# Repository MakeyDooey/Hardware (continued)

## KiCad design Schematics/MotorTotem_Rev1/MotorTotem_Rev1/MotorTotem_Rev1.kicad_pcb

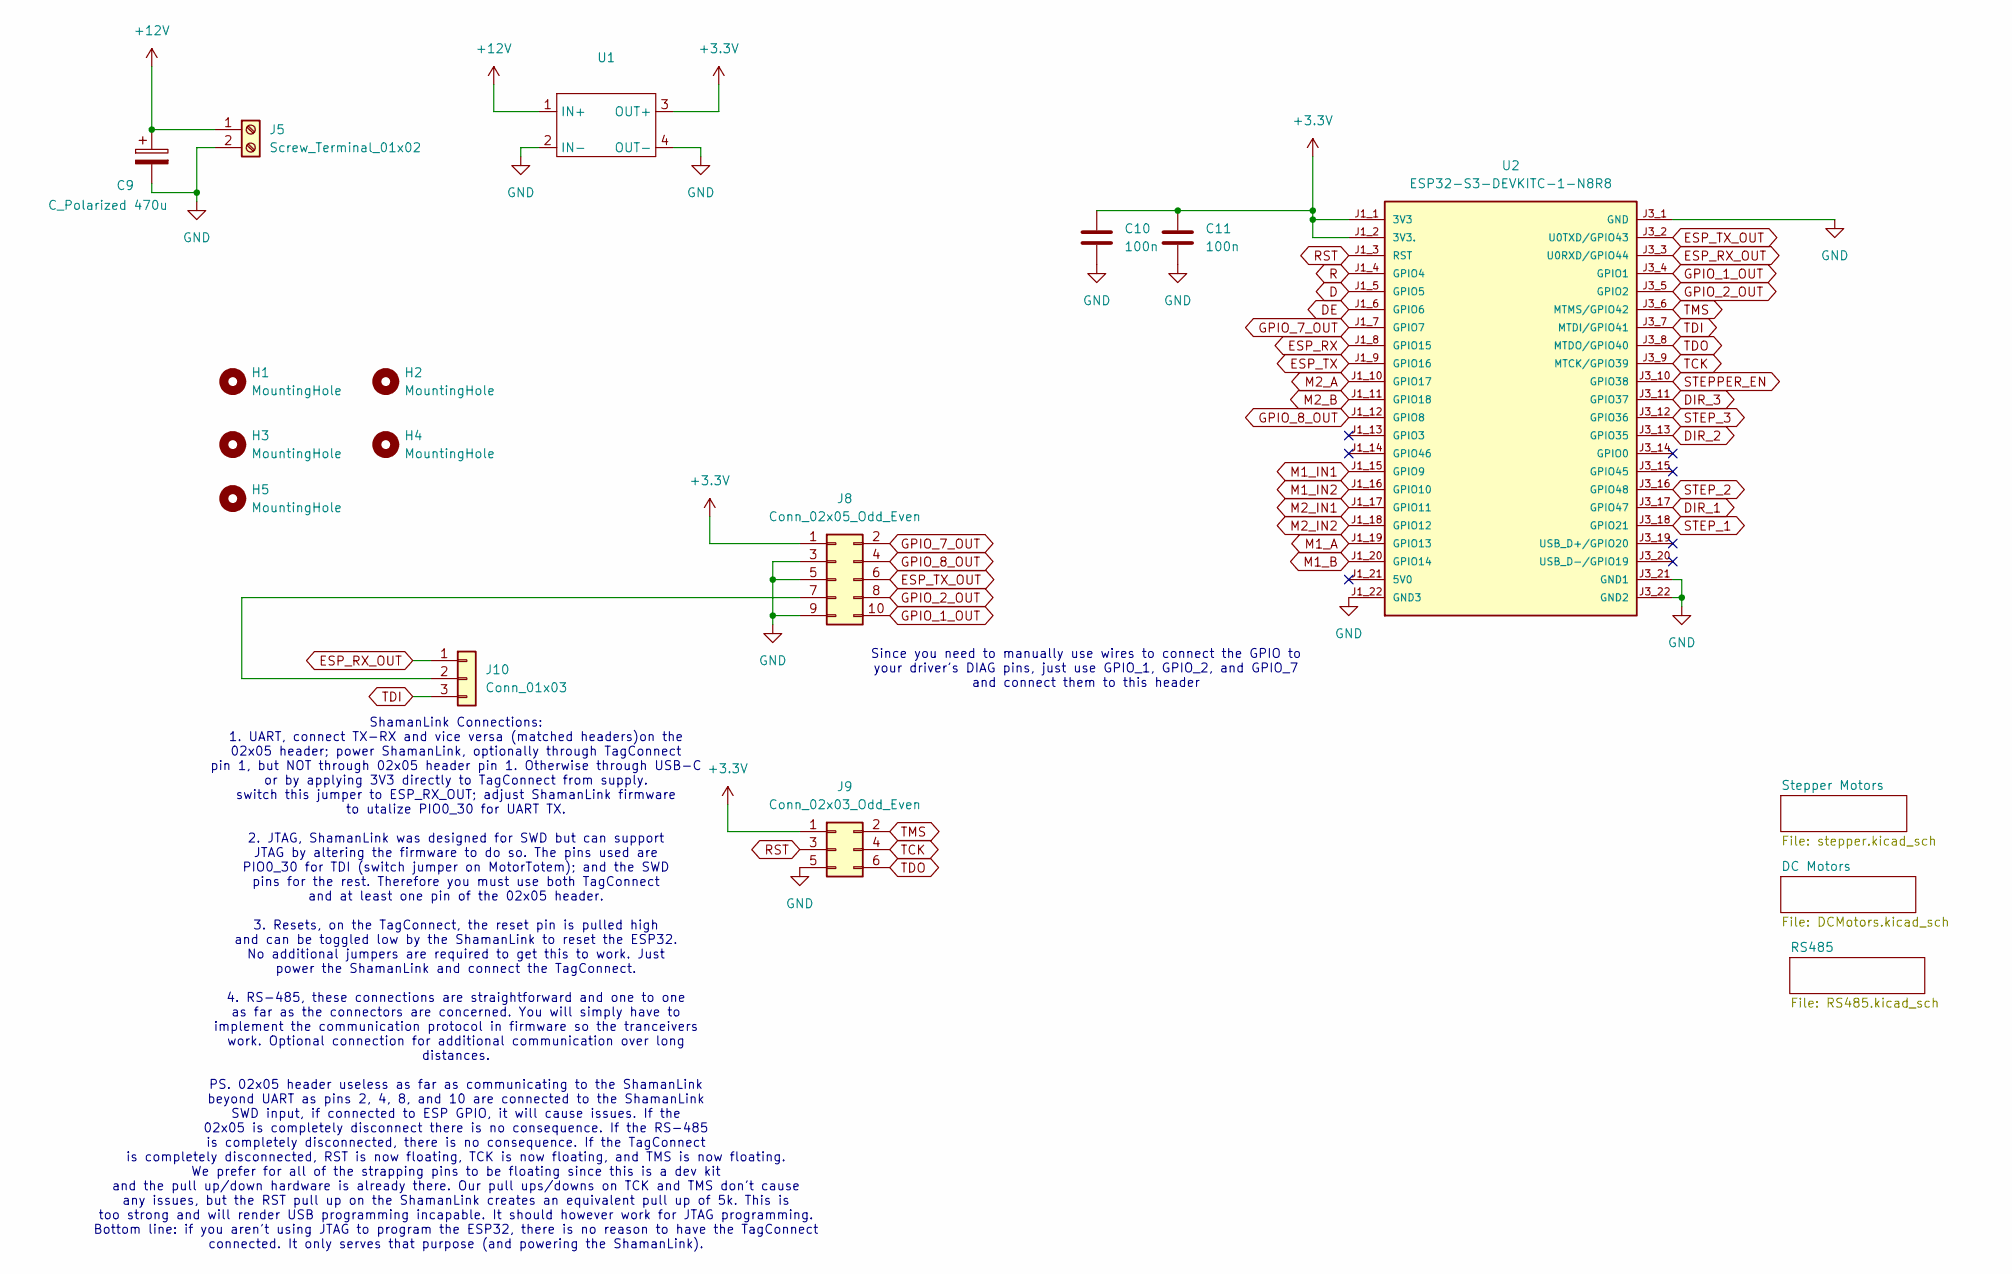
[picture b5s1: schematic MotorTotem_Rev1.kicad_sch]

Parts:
C9: C_Polarized 470u; CP_Radial_D6.3mm_P2.50mm
C10, C11: 100n; C_0805_2012Metric_Pad1.18x1.45mm_HandSolder
H1, H2, H3, H4, H5: MountingHole; MountingHole_2.5mm_Pad_TopOnly
J5: Screw_Terminal_01x02; TerminalBlock_Phoenix_MKDS-1,5-2-5.08_1x02_P5.08mm_Horizont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
J8: Conn_02x05_Odd_Even; PinHeader_2x05_P2.54mm_Vertical
J9: Conn_02x03_Odd_Even; PinHeader_2x03_P2.54mm_Vertical
J10: Conn_01x03; PinHeader_1x03_P2.54mm_Vertical
U1: LM2596BuckBoost
U2: ESP32-S3-DEVKITC-1-N8R8

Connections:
+3.3V: C10.1, C11.1, J8.1, J9.1, U1.3 (OUT+), U2.J1_1 (3V3), U2.J1_2 (3V3.); also elsewhere on the board
+12V: C9.1, J5.1, U1.1 (IN+); also elsewhere on the board
D: U2.J1_5 (GPIO5); also elsewhere on the board
DE: U2.J1_6 (GPIO6); also elsewhere on the board
DIR_1: U2.J3_17 (GPIO47); also elsewhere on the board
DIR_2: U2.J3_13 (GPIO35); also elsewhere on the board
DIR_3: U2.J3_11 (GPIO37); also elsewhere on the board
ESP_RX: U2.J1_8 (GPIO15); also elsewhere on the board
ESP_RX_OUT: J10.1, U2.J3_3 (U0RXD/GPIO44)
ESP_TX: U2.J1_9 (GPIO16); also elsewhere on the board
ESP_TX_OUT: J8.6, U2.J3_2 (U0TXD/GPIO43)
GND: C9.2, C10.2, C11.2, J5.2, J8.3, J8.5, J8.9, J9.5, U1.2 (IN-), U1.4 (OUT-), U2.J1_22 (GND3), U2.J3_1 (GND), U2.J3_21 (GND1), U2.J3_22 (GND2); also elsewhere on the board
GPIO_1_OUT: J8.10, U2.J3_4 (GPIO1)
GPIO_2_OUT: J8.8, U2.J3_5 (GPIO2)
GPIO_7_OUT: J8.2, U2.J1_7 (GPIO7)
GPIO_8_OUT: J8.4, U2.J1_12 (GPIO8)
M1_A: U2.J1_19 (GPIO13); also elsewhere on the board
M1_B: U2.J1_20 (GPIO14); also elsewhere on the board
M1_IN1: U2.J1_15 (GPIO9); also elsewhere on the board
M1_IN2: U2.J1_16 (GPIO10); also elsewhere on the board
M2_A: U2.J1_10 (GPIO17); also elsewhere on the board
M2_B: U2.J1_11 (GPIO18); also elsewhere on the board
M2_IN1: U2.J1_17 (GPIO11); also elsewhere on the board
M2_IN2: U2.J1_18 (GPIO12); also elsewhere on the board
unnamed: J8.7, J10.2
R: U2.J1_4 (GPIO4); also elsewhere on the board
RST: J9.3, U2.J1_3 (RST)
STEPPER_EN: U2.J3_10 (GPIO38); also elsewhere on the board
STEP_1: U2.J3_18 (GPIO21); also elsewhere on the board
STEP_2: U2.J3_16 (GPIO48); also elsewhere on the board
STEP_3: U2.J3_12 (GPIO36); also elsewhere on the board
TCK: J9.4, U2.J3_9 (MTCK/GPIO39)
TDI: J10.3, U2.J3_7 (MTDI/GPIO41)
TDO: J9.6, U2.J3_8 (MTDO/GPIO40)
TMS: J9.2, U2.J3_6 (MTMS/GPIO42)

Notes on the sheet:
Since you need to manually use wires to connect the GPIO to your driver's DIAG pins, just use GPIO_1, GPIO_2, and GPIO_7 and connect them to this header
ShamanLink Connections: 1. UART, connect TX-RX and vice versa (matched headers)on the 02x05 header; power ShamanLink, optionally through TagConnect pin 1, but NOT through 02x05 header pin 1. Otherwise through USB-C or by applying 3V3 directly to TagConnect from supply. switch this jumper to ESP_RX_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

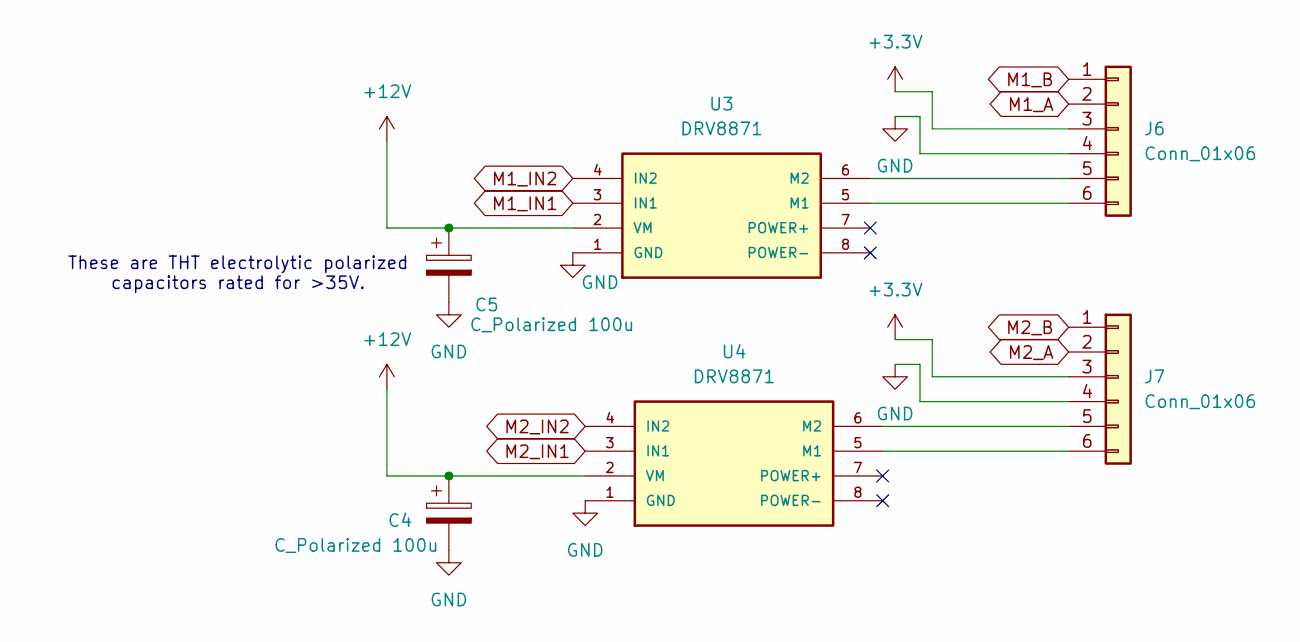
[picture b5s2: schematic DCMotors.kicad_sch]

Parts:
C4, C5: C_Polarized 100u; CP_Radial_D6.3mm_P2.50mm
J6, J7: Conn_01x06; PinHeader_1x06_P2.54mm_Vertical
U3, U4: DRV8871

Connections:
+3.3V: J6.3, J7.3; also elsewhere on the board
+12V: C4.1, C5.1, U3.2 (VM), U4.2 (VM); also elsewhere on the board
GND: C4.2, C5.2, J6.4, J7.4, U3.1 (GND), U4.1 (GND); also elsewhere on the board
M1_A: J6.2; also elsewhere on the board
M1_B: J6.1; also elsewhere on the board
M1_IN1: U3.3 (IN1); also elsewhere on the board
M1_IN2: U3.4 (IN2); also elsewhere on the board
M2_A: J7.2; also elsewhere on the board
M2_B: J7.1; also elsewhere on the board
M2_IN1: U4.3 (IN1); also elsewhere on the board
M2_IN2: U4.4 (IN2); also elsewhere on the board
unnamed: J6.5, U3.6 (M2)
unnamed: J6.6, U3.5 (M1)
unnamed: J7.5, U4.6 (M2)
unnamed: J7.6, U4.5 (M1)

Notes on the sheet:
These are THT electrolytic polarized capacitors rated for >35V.

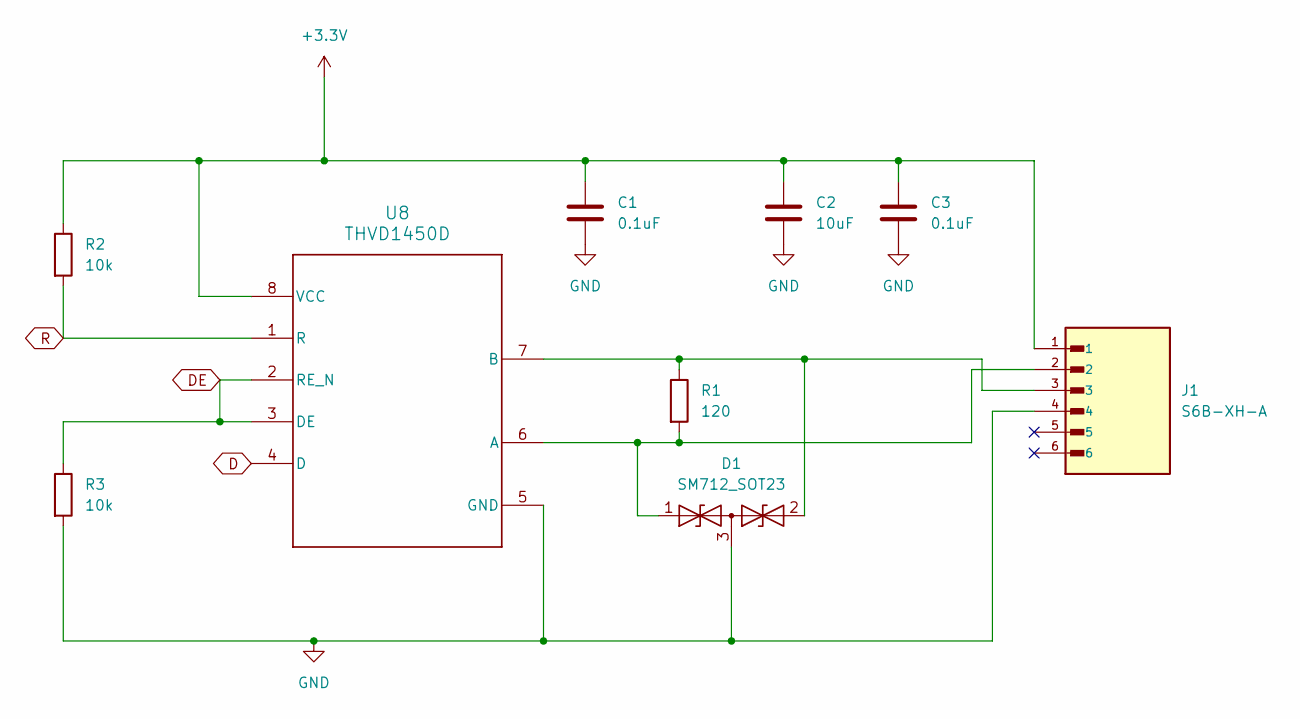
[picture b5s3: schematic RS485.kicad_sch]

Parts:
C1, C3: 0.1uF; C_0805_2012Metric_Pad1.18x1.45mm_HandSolder
C2: 10uF; C_0805_2012Metric_Pad1.18x1.45mm_HandSolder
D1: SM712_SOT23; SOT-23
J1: S6B-XH-A; JST_S6B-XH-A
R1: 120; R_1206_3216Metric_Pad1.30x1.75mm_HandSolder
R2, R3: 10k; R_0805_2012Metric_Pad1.20x1.40mm_HandSolder
U8: THVD1450D; D0008A_M

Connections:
+3.3V: C1.1, C2.1, C3.1, J1.1, R2.1, U8.8 (VCC); also elsewhere on the board
D: U8.4 (D); also elsewhere on the board
DE: R3.1, U8.2 (RE_N), U8.3 (DE); also elsewhere on the board
GND: C1.2, C2.2, C3.2, D1.3 (common), J1.4, R3.2, U8.5 (GND); also elsewhere on the board
unnamed: D1.1 (A1), J1.2, R1.2, U8.6 (A)
unnamed: D1.2 (A2), J1.3, R1.1, U8.7 (B)
R: R2.2, U8.1 (R); also elsewhere on the board

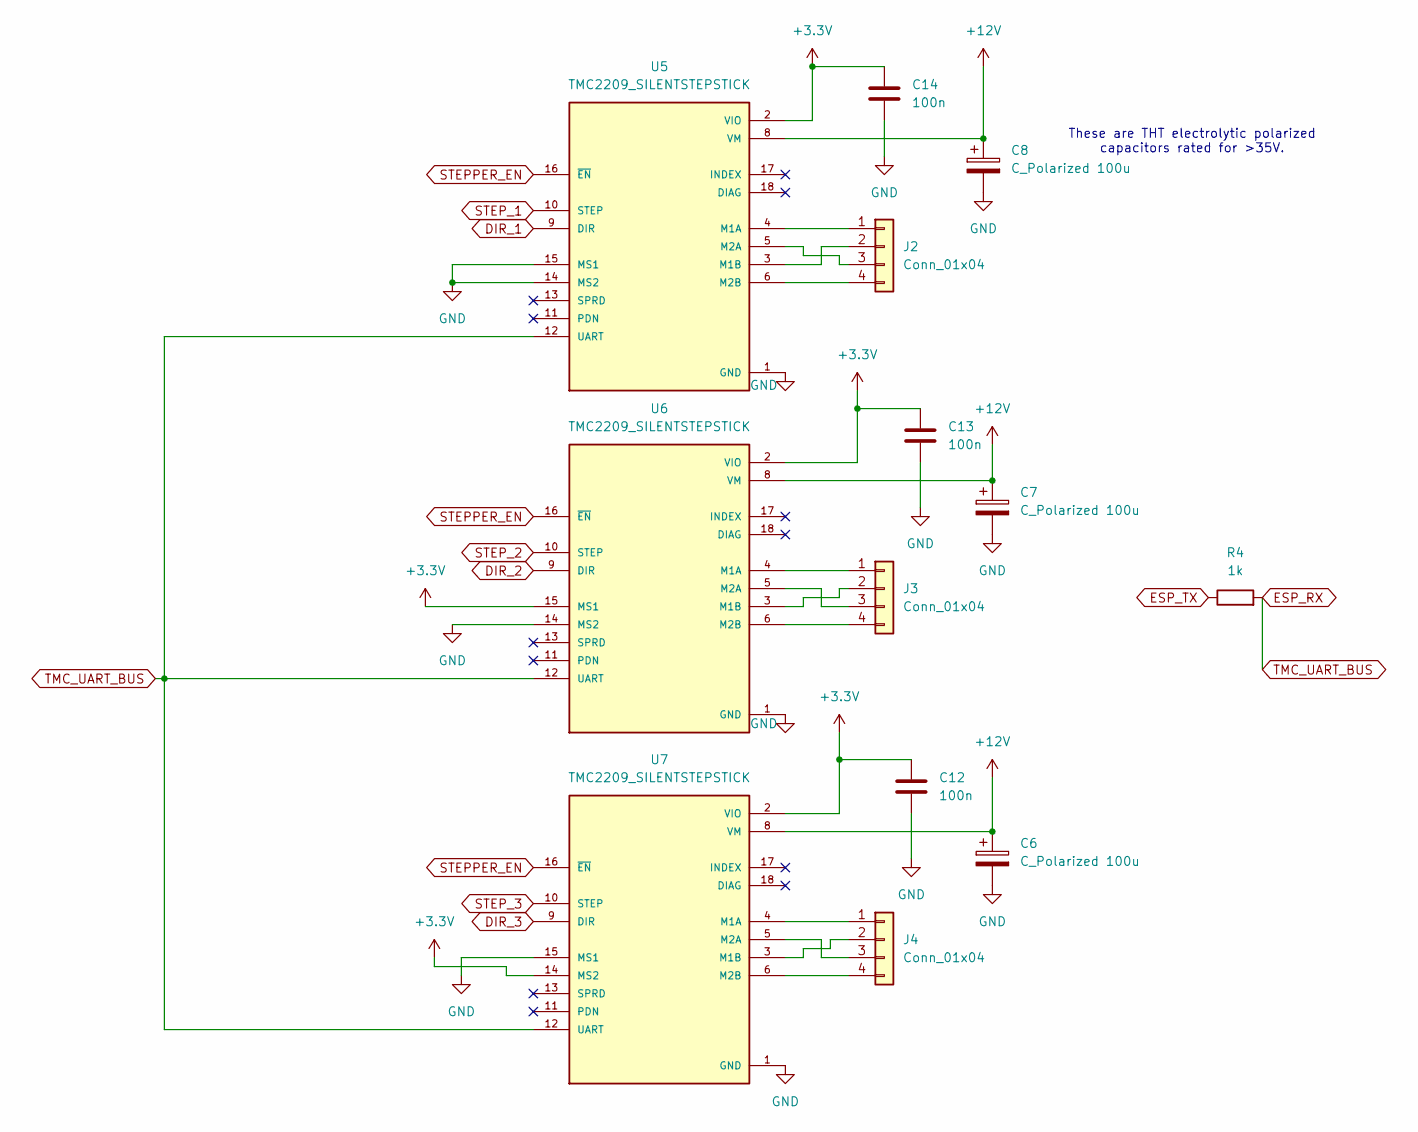
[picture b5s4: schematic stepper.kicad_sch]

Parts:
C6, C7, C8: C_Polarized 100u; CP_Radial_D6.3mm_P2.50mm
C12, C13, C14: 100n; C_0805_2012Metric_Pad1.18x1.45mm_HandSolder
J2, J3, J4: Conn_01x04; PinHeader_1x04_P2.54mm_Vertical
R4: 1k; R_0805_2012Metric_Pad1.20x1.40mm_HandSolder
U5, U6, U7: TMC2209_SILENTSTEPSTICK; MODULE_TMC2209_SILENTSTEPSTICK; PARTREV 1.20

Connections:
+3.3V: C12.1, C13.1, C14.1, U5.2 (VIO), U6.2 (VIO), U6.15 (MS1), U7.2 (VIO), U7.14 (MS2); also elsewhere on the board
+12V: C6.1, C7.1, C8.1, U5.8 (VM), U6.8 (VM), U7.8 (VM); also elsewhere on the board
DIR_1: U5.9 (DIR); also elsewhere on the board
DIR_2: U6.9 (DIR); also elsewhere on the board
DIR_3: U7.9 (DIR); also elsewhere on the board
ESP_RX: R4.2, U5.12 (UART), U6.12 (UART), U7.12 (UART); also elsewhere on the board
ESP_TX: R4.1; also elsewhere on the board
GND: C6.2, C7.2, C8.2, C12.2, C13.2, C14.2, U5.1 (GND), U5.7 (GND), U5.14 (MS2), U5.15 (MS1), U6.1 (GND), U6.7 (GND), U6.14 (MS2), U7.1 (GND), U7.7 (GND), U7.15 (MS1); also elsewhere on the board
unnamed: J2.1, U5.4 (M1A)
unnamed: J2.2, U5.3 (M1B)
unnamed: J2.3, U5.5 (M2A)
unnamed: J2.4, U5.6 (M2B)
unnamed: J3.1, U6.4 (M1A)
unnamed: J3.2, U6.3 (M1B)
unnamed: J3.3, U6.5 (M2A)
unnamed: J3.4, U6.6 (M2B)
unnamed: J4.1, U7.4 (M1A)
unnamed: J4.2, U7.3 (M1B)
unnamed: J4.3, U7.5 (M2A)
unnamed: J4.4, U7.6 (M2B)
STEPPER_EN: U5.16 (~EN), U6.16 (~EN), U7.16 (~EN); also elsewhere on the board
STEP_1: U5.10 (STEP); also elsewhere on the board
STEP_2: U6.10 (STEP); also elsewhere on the board
STEP_3: U7.10 (STEP); also elsewhere on the board

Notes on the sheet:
These are THT electrolytic polarized capacitors rated for >35V.

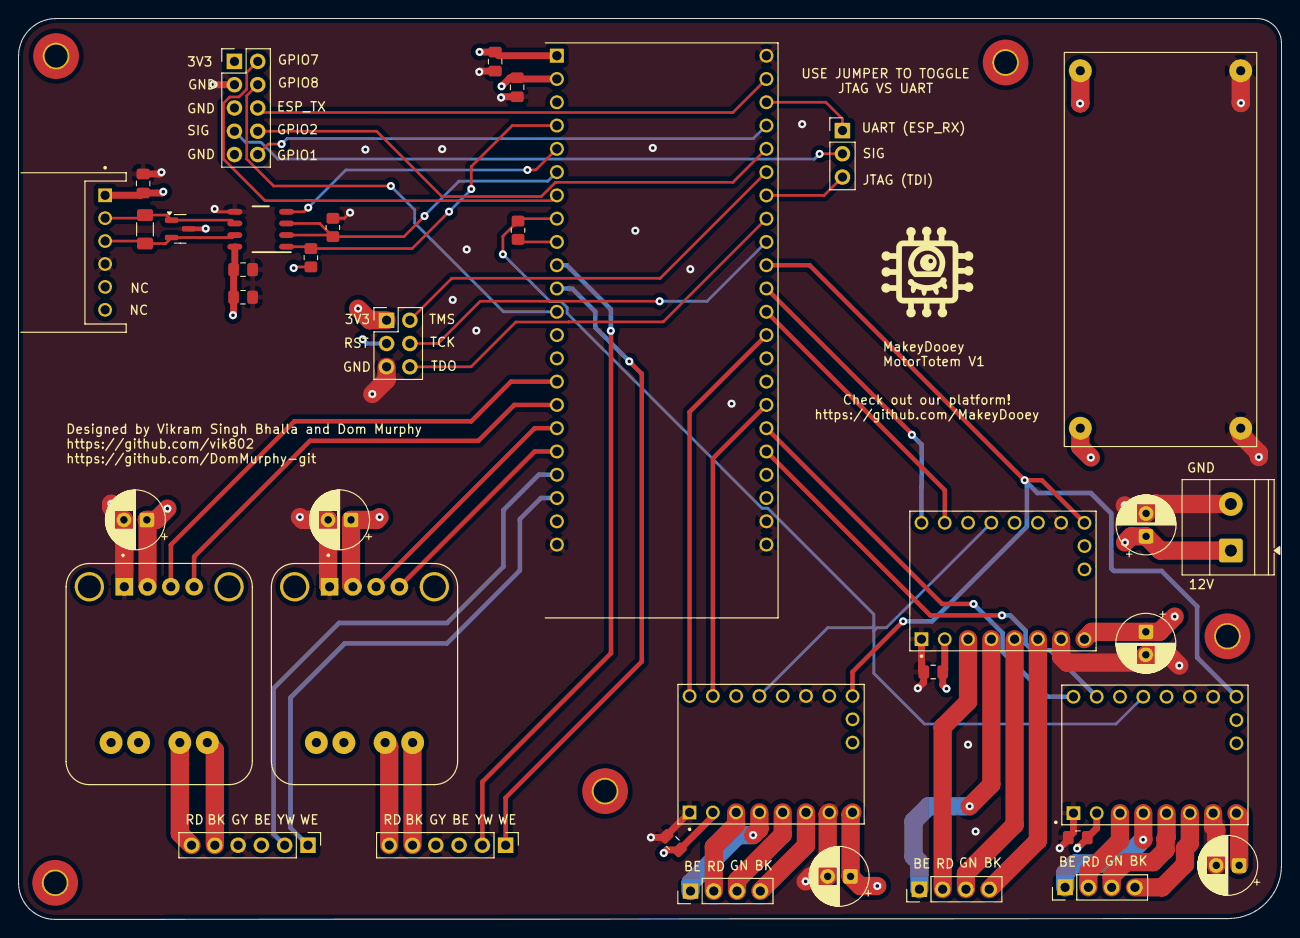
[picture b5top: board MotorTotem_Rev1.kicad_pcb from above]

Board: 4 copper layers, 137.8 x 98.3 mm, 42 parts (0 on the bottom side), 53 nets.

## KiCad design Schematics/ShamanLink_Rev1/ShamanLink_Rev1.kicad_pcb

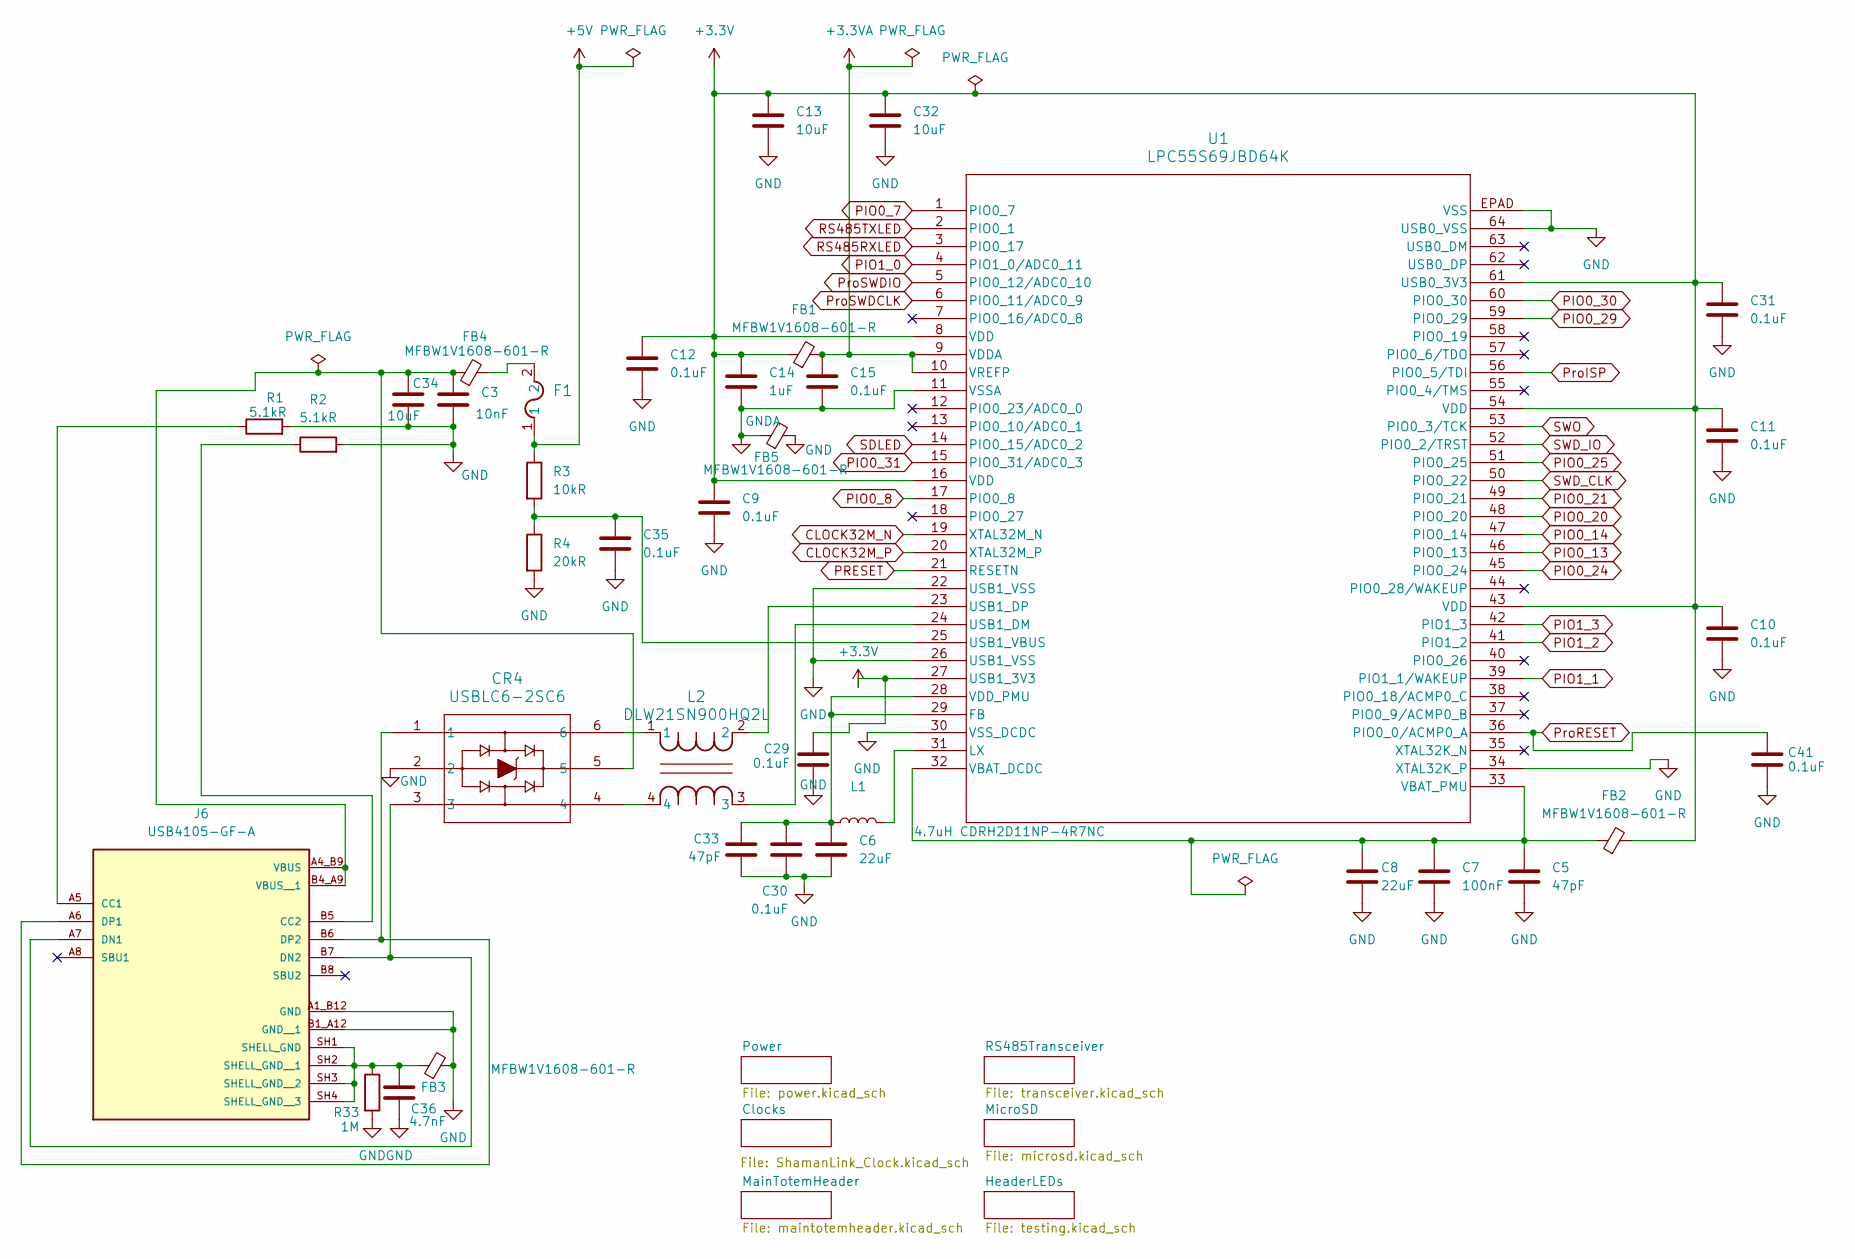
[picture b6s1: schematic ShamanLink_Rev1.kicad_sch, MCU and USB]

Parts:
C3: 10nF; C_0805_2012Metric_Pad1.18x1.45mm_HandSolder
C5, C33: 47pF; C_0805_2012Metric_Pad1.18x1.45mm_HandSolder
C6, C8: 22uF; C_1206_3216Metric_Pad1.33x1.80mm_HandSolder
C7: 100nF; C_0805_2012Metric_Pad1.18x1.45mm_HandSolder
C9, C10, C11, C12, C15, C29, C30, C31, C35, C41: 0.1uF; C_0805_2012Metric_Pad1.18x1.45mm_HandSolder
C13, C32, C34: 10uF; C_0805_2012Metric_Pad1.18x1.45mm_HandSolder
C14: 1uF; C_0805_2012Metric_Pad1.18x1.45mm_HandSolder
C36: 4.7nF; C_0805_2012Metric_Pad1.18x1.45mm_HandSolder
CR4: USBLC6-2SC6; SOT23-6L_STM-M
F1: 1206L075/13.2WR; 1206LSeries_LTF-M
FB1, FB2, FB3, FB4, FB5: MFBW1V1608-601-R; R_0603_1608Metric_Pad0.98x0.95mm_HandSolder
J6: USB4105-GF-A; GCT_USB4105-GF-A; PARTREV B4
L1: 4.7uH CDRH2D11NP-4R7NC; Inductor_Sumida_CDRH2D11
L2: DLW21SN900HQ2L; IND_DLW21S_0805_MUR-M
R1, R2: 5.1kR; R_0805_2012Metric_Pad1.20x1.40mm_HandSolder
R3: 10kR; R_0805_2012Metric_Pad1.20x1.40mm_HandSolder
R4: 20kR; R_0805_2012Metric_Pad1.20x1.40mm_HandSolder
R33: 1M; R_0805_2012Metric_Pad1.20x1.40mm_HandSolder
U1: LPC55S69JBD64K; HTQFP64_SOT855-5_NXP-M

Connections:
+3.3V: C9.1, C10.1, C11.1, C12.1, C13.1, C14.1, C29.1, C31.1, C32.1, FB1.1, FB2.2, U1.8 (VDD), U1.16 (VDD), U1.27 (USB1_3V3), U1.43 (VDD), U1.54 (VDD), U1.61 (USB0_3V3); also elsewhere on the board
+3.3VA: C15.1, FB1.2, U1.9 (VDDA), U1.10 (VREFP)
+5V: F1.1, R3.1; also elsewhere on the board
CLOCK32M_N: U1.19 (XTAL32M_N); also elsewhere on the board
CLOCK32M_P: U1.20 (XTAL32M_P); also elsewhere on the board
GND: C3.2, C5.2, C6.2, C7.2, C8.2, C9.2, C10.2, C11.2, C12.2, C13.2, C29.2, C30.2, C31.2, C32.2, C33.2, C34.2, C35.2, C36.2, C41.2, CR4.2, FB3.2, FB5.2, J6.A1_B12 (GND), J6.B1_A12 (GND__1), R1.2, R2.2, R4.2, R33.2, U1.22 (USB1_VSS), U1.26 (USB1_VSS), U1.30 (VSS_DCDC), U1.34 (XTAL32K_P), U1.64 (USB0_VSS), U1.EPAD (VSS); also elsewhere on the board
GNDA: C14.2, C15.2, FB5.1, U1.11 (VSSA)
unnamed: CR4.4, L2.4
unnamed: CR4.6, L2.1
unnamed: F1.2, FB4.2
unnamed: J6.A5 (CC1), R1.1
unnamed: J6.B5 (CC2), R2.1
unnamed: CR4.3, J6.A7 (DN1), J6.B7 (DN2)
unnamed: CR4.1, J6.A6 (DP1), J6.B6 (DP2)
unnamed: C36.1, FB3.1, J6.SH1 (SHELL_GND), J6.SH2 (SHELL_GND__1), J6.SH3 (SHELL_GND__2), J6.SH4 (SHELL_GND__3), R33.1
unnamed: C3.1, C34.1, CR4.5, FB4.1, J6.A4_B9 (VBUS), J6.B4_A9 (VBUS__1)
unnamed: C6.1, C30.1, C33.1, L1.1, U1.28 (VDD_PMU), U1.29 (FB)
unnamed: L1.2, U1.31 (LX)
unnamed: L2.3, U1.24 (USB1_DM)
unnamed: L2.2, U1.23 (USB1_DP)
unnamed: C35.1, R3.2, R4.1, U1.25 (USB1_VBUS)
unnamed: C5.1, C7.1, C8.1, FB2.1, U1.32 (VBAT_DCDC), U1.33 (VBAT_PMU)
PIO0_7: U1.1 (PIO0_7); also elsewhere on the board
PIO0_8: U1.17 (PIO0_8); also elsewhere on the board
PIO0_13: U1.46 (PIO0_13); also elsewhere on the board
PIO0_14: U1.47 (PIO0_14); also elsewhere on the board
PIO0_20: U1.48 (PIO0_20); also elsewhere on the board
PIO0_21: U1.49 (PIO0_21); also elsewhere on the board
PIO0_24: U1.45 (PIO0_24); also elsewhere on the board
PIO0_25: U1.51 (PIO0_25); also elsewhere on the board
PIO0_29: U1.59 (PIO0_29); also elsewhere on the board
PIO0_30: U1.60 (PIO0_30); also elsewhere on the board
PIO0_31: U1.15 (PIO0_31/ADC0_3); also elsewhere on the board
PIO1_0: U1.4 (PIO1_0/ADC0_11); also elsewhere on the board
PIO1_1: U1.39 (PIO1_1/WAKEUP); also elsewhere on the board
PIO1_2: U1.41 (PIO1_2); also elsewhere on the board
PIO1_3: U1.42 (PIO1_3); also elsewhere on the board
PRESET: U1.21 (RESETN); also elsewhere on the board
ProISP: U1.56 (PIO0_5/TDI); also elsewhere on the board
ProRESET: C41.1, U1.36 (PIO0_0/ACMP0_A); also elsewhere on the board
ProSWDCLK: U1.6 (PIO0_11/ADC0_9); also elsewhere on the board
ProSWDIO: U1.5 (PIO0_12/ADC0_10); also elsewhere on the board
RS485RXLED: U1.3 (PIO0_17); also elsewhere on the board
RS485TXLED: U1.2 (PIO0_1); also elsewhere on the board
SDLED: U1.14 (PIO0_15/ADC0_2); also elsewhere on the board
SWD_CLK: U1.50 (PIO0_22); also elsewhere on the board
SWD_IO: U1.52 (PIO0_2/TRST); also elsewhere on the board
SWO: U1.53 (PIO0_3/TCK); also elsewhere on the board

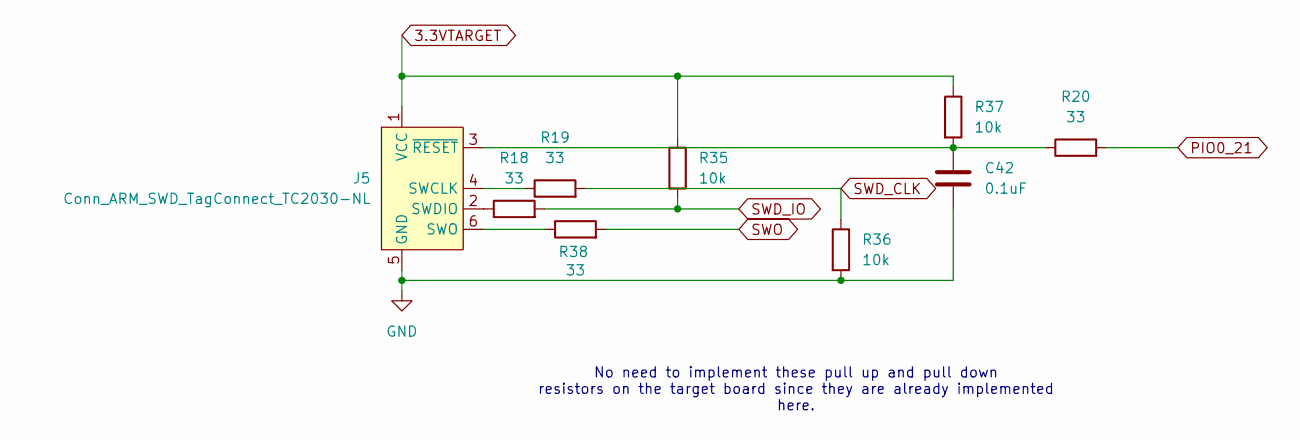
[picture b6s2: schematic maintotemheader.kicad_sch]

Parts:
C42: 0.1uF; C_0805_2012Metric_Pad1.18x1.45mm_HandSolder
J5: Conn_ARM_SWD_TagConnect_TC2030-NL; Tag-Connect_TC2030-IDC-NL_2x03_P1.27mm_Vertical
R18, R19, R20, R38: 33; R_0805_2012Metric_Pad1.20x1.40mm_HandSolder
R35, R36, R37: 10k; R_0805_2012Metric_Pad1.20x1.40mm_HandSolder

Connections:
3.3VTARGET: J5.1 (VCC), R35.1, R37.1; also elsewhere on the board
GND: C42.2, J5.5 (GND), R36.2; also elsewhere on the board
unnamed: J5.4 (SWCLK), R19.1
unnamed: J5.2 (SWDIO), R18.1
unnamed: J5.6 (SWO), R38.1
unnamed: C42.1, J5.3 (~RESET), R20.1, R37.2
PIO0_21: R20.2; also elsewhere on the board
SWD_CLK: R19.2, R36.1; also elsewhere on the board
SWD_IO: R18.2, R35.2; also elsewhere on the board
SWO: R38.2; also elsewhere on the board

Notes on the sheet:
No need to implement these pull up and pull down resistors on the target board since they are already implemented here.

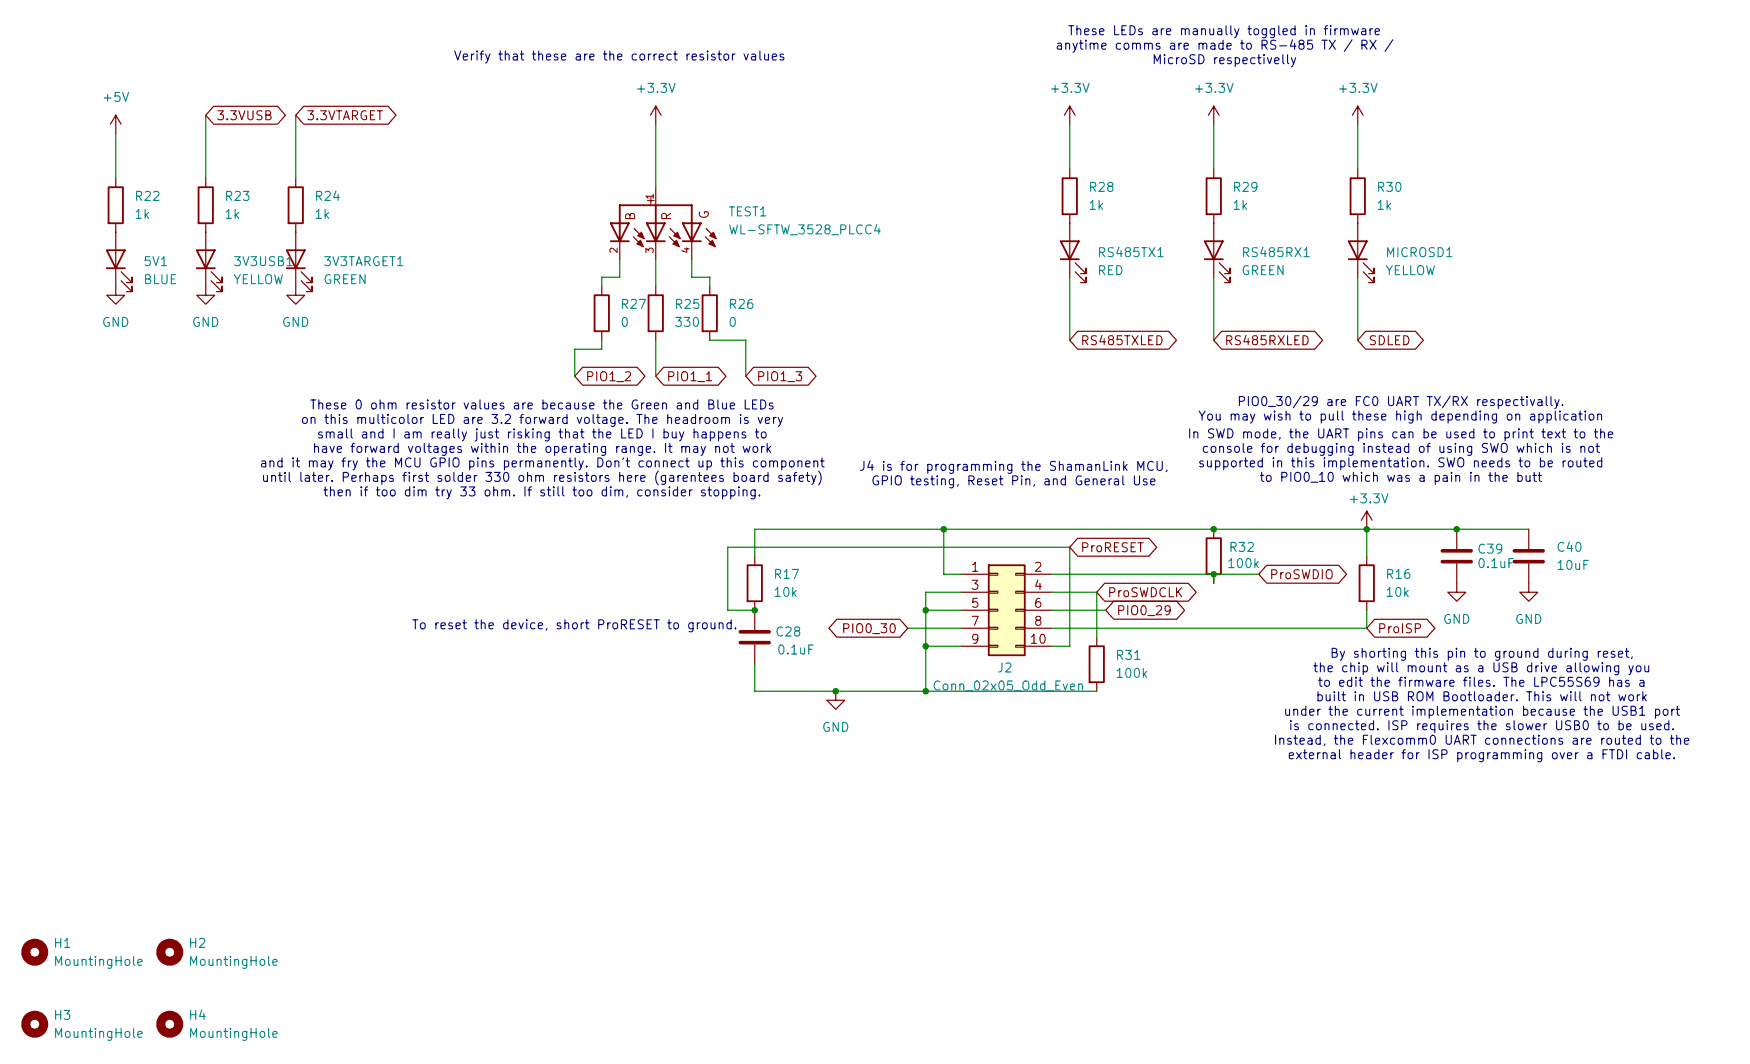
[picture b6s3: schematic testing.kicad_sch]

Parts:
3V3TARGET1: GREEN; LED_0805_2012Metric_Pad1.15x1.40mm_HandSolder
3V3USB1: YELLOW; LED_0805_2012Metric_Pad1.15x1.40mm_HandSolder
5V1: BLUE; LED_0805_2012Metric_Pad1.15x1.40mm_HandSolder
C28, C39: 0.1uF; C_0805_2012Metric_Pad1.18x1.45mm_HandSolder
C40: 10uF; C_0805_2012Metric_Pad1.18x1.45mm_HandSolder
H1, H2, H3, H4: MountingHole; MountingHole_3mm_Pad_TopOnly
J2: Conn_02x05_Odd_Even; PinHeader_2x05_P2.54mm_Vertical
MICROSD1: YELLOW; LED_0805_2012Metric_Pad1.15x1.40mm_HandSolder
R16, R17: 10k; R_0805_2012Metric_Pad1.20x1.40mm_HandSolder
R22, R23, R24, R28, R29, R30: 1k; R_0805_2012Metric_Pad1.20x1.40mm_HandSolder
R25: 330; R_0805_2012Metric_Pad1.20x1.40mm_HandSolder
R26, R27: 0; R_0805_2012Metric_Pad1.20x1.40mm_HandSolder
R31, R32: 100k; R_0805_2012Metric_Pad1.20x1.40mm_HandSolder
RS485RX1: GREEN; LED_0805_2012Metric_Pad1.15x1.40mm_HandSolder
RS485TX1: RED; LED_0805_2012Metric_Pad1.15x1.40mm_HandSolder
TEST1: WL-SFTW_3528_PLCC4; multicolorLED

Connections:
3.3VTARGET: R24.1; also elsewhere on the board
3.3VUSB: R23.1; also elsewhere on the board
+3.3V: C39.1, C40.1, J2.1, R16.1, R17.1, R28.1, R29.1, R30.1, R32.1, TEST1.1; also elsewhere on the board
+5V: R22.1; also elsewhere on the board
GND: 3V3TARGET1.1 (K), 3V3USB1.1 (K), 5V1.1 (K), C28.2, C39.2, C40.2, J2.3, J2.5, J2.9, R31.2; also elsewhere on the board
unnamed: 3V3TARGET1.2 (A), R24.2
unnamed: 3V3USB1.2 (A), R23.2
unnamed: 5V1.2 (A), R22.2
unnamed: MICROSD1.2 (A), R30.2
unnamed: R25.1, TEST1.3
unnamed: R26.1, TEST1.4
unnamed: R27.1, TEST1.2
unnamed: R29.2, RS485RX1.2 (A)
unnamed: R28.2, RS485TX1.2 (A)
PIO0_29: J2.6; also elsewhere on the board
PIO0_30: J2.7; also elsewhere on the board
PIO1_1: R25.2; also elsewhere on the board
PIO1_2: R27.2; also elsewhere on the board
PIO1_3: R26.2; also elsewhere on the board
ProISP: J2.8, R16.2; also elsewhere on the board
ProRESET: C28.1, J2.10, R17.2; also elsewhere on the board
ProSWDCLK: J2.4, R31.1; also elsewhere on the board
ProSWDIO: J2.2, R32.2; also elsewhere on the board
RS485RXLED: RS485RX1.1 (K); also elsewhere on the board
RS485TXLED: RS485TX1.1 (K); also elsewhere on the board
SDLED: MICROSD1.1 (K); also elsewhere on the board

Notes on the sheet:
These LEDs are manually toggled in firmware anytime comms are made to RS-485 TX / RX / MicroSD respectivelly
To reset the device, short ProRESET to ground.
In SWD mode, the UART pins can be used to print text to the console for debugging instead of using SWO which is not supported in this implementation. SWO needs to be routed to PIO0_10 which was a pain in the butt
Verify that these are the correct resistor values
By shorting this pin to ground during reset, the chip will mount as a USB drive allowing you to edit the firmware files. The LPC55S69 has a built in USB ROM Bootloader. This will not work under the current implementation because the USB1 port is connected. ISP requires the slower USB0 to be used. I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
PIO0_30/29 are FC0 UART TX/RX respectivally. You may wish to pull these high depending on application
J4 is for programming the ShamanLink MCU, GPIO testing, Reset Pin, and General Use
These 0 ohm resistor values are because the Green and Blue LEDs on this multicolor LED are 3.2 forward voltage. The headroom is very small and I am really just risking that the LED I buy happens to have forward voltages within the operating range. It may not work and it may fry the MCU GPIO pins pe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

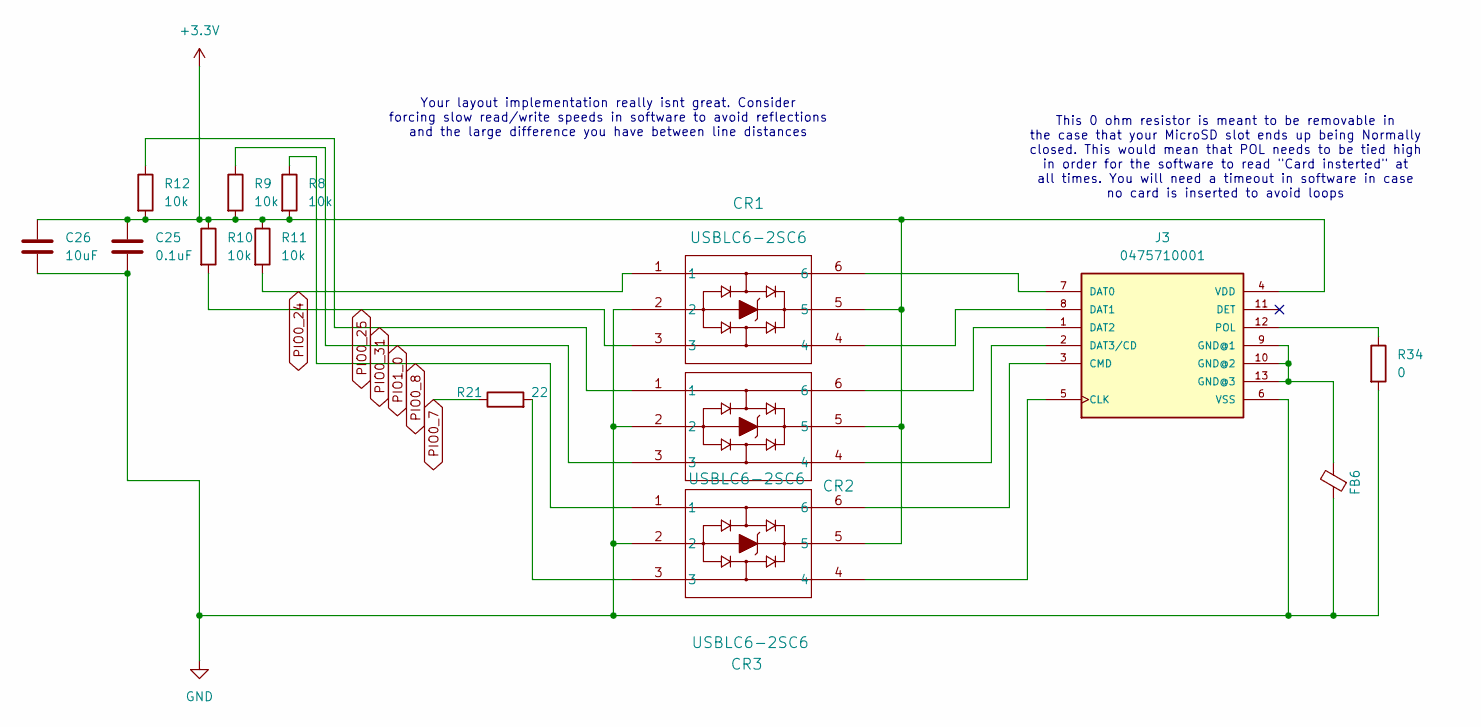
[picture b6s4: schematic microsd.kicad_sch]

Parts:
C25: 0.1uF; C_0805_2012Metric_Pad1.18x1.45mm_HandSolder
C26: 10uF; C_0805_2012Metric_Pad1.18x1.45mm_HandSolder
CR1, CR2, CR3: USBLC6-2SC6; SOT23-6L_STM-M
FB6: MFBW1V1608-601-R; R_0603_1608Metric_Pad0.98x0.95mm_HandSolder
J3: 0475710001; MOLEX_0475710001
R8, R9, R10, R11, R12: 10k; R_0805_2012Metric_Pad1.20x1.40mm_HandSolder
R21: 22; R_0805_2012Metric_Pad1.20x1.40mm_HandSolder
R34: 0; R_0805_2012Metric_Pad1.20x1.40mm_HandSolder

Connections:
+3.3V: C25.1, C26.1, CR1.5, CR2.5, CR3.5, J3.4 (VDD), R8.2, R9.2, R10.1, R11.1, R12.2; also elsewhere on the board
GND: C25.2, C26.2, CR1.2, CR2.2, CR3.2, FB6.1, J3.6 (VSS), R34.2; also elsewhere on the board
unnamed: CR3.3, R21.2
unnamed: CR3.4, J3.5 (CLK)
unnamed: CR3.6, J3.3 (CMD)
unnamed: CR1.6, J3.7 (DAT0)
unnamed: CR1.4, J3.8 (DAT1)
unnamed: CR2.6, J3.1 (DAT2)
unnamed: CR2.4, J3.2 (DAT3/CD)
unnamed: FB6.2, J3.9 (GND@1), J3.10 (GND@2), J3.13 (GND@3)
unnamed: J3.12 (POL), R34.1
PIO0_7: R21.1; also elsewhere on the board
PIO0_8: CR3.1, R8.1; also elsewhere on the board
PIO0_24: CR1.1, R11.2; also elsewhere on the board
PIO0_25: CR1.3, R10.2; also elsewhere on the board
PIO0_31: CR2.1, R12.1; also elsewhere on the board
PIO1_0: CR2.3, R9.1; also elsewhere on the board

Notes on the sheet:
This 0 ohm resistor is meant to be removable in the case that your MicroSD slot ends up being Normally closed. This would mean that POL needs to be tied high in order for the software to read "Card insterted" at all times. You will need a timeout in software in case no card is inserted to avoid loo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
Your layout implementation really isnt great. Consider forcing slow read/write speeds in software to avoid reflections and the large difference you have between line distances
